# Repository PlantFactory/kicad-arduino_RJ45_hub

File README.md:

# kicad-arduino_RJ45_hub
The board implements 4 port I2C hub via RJ45.

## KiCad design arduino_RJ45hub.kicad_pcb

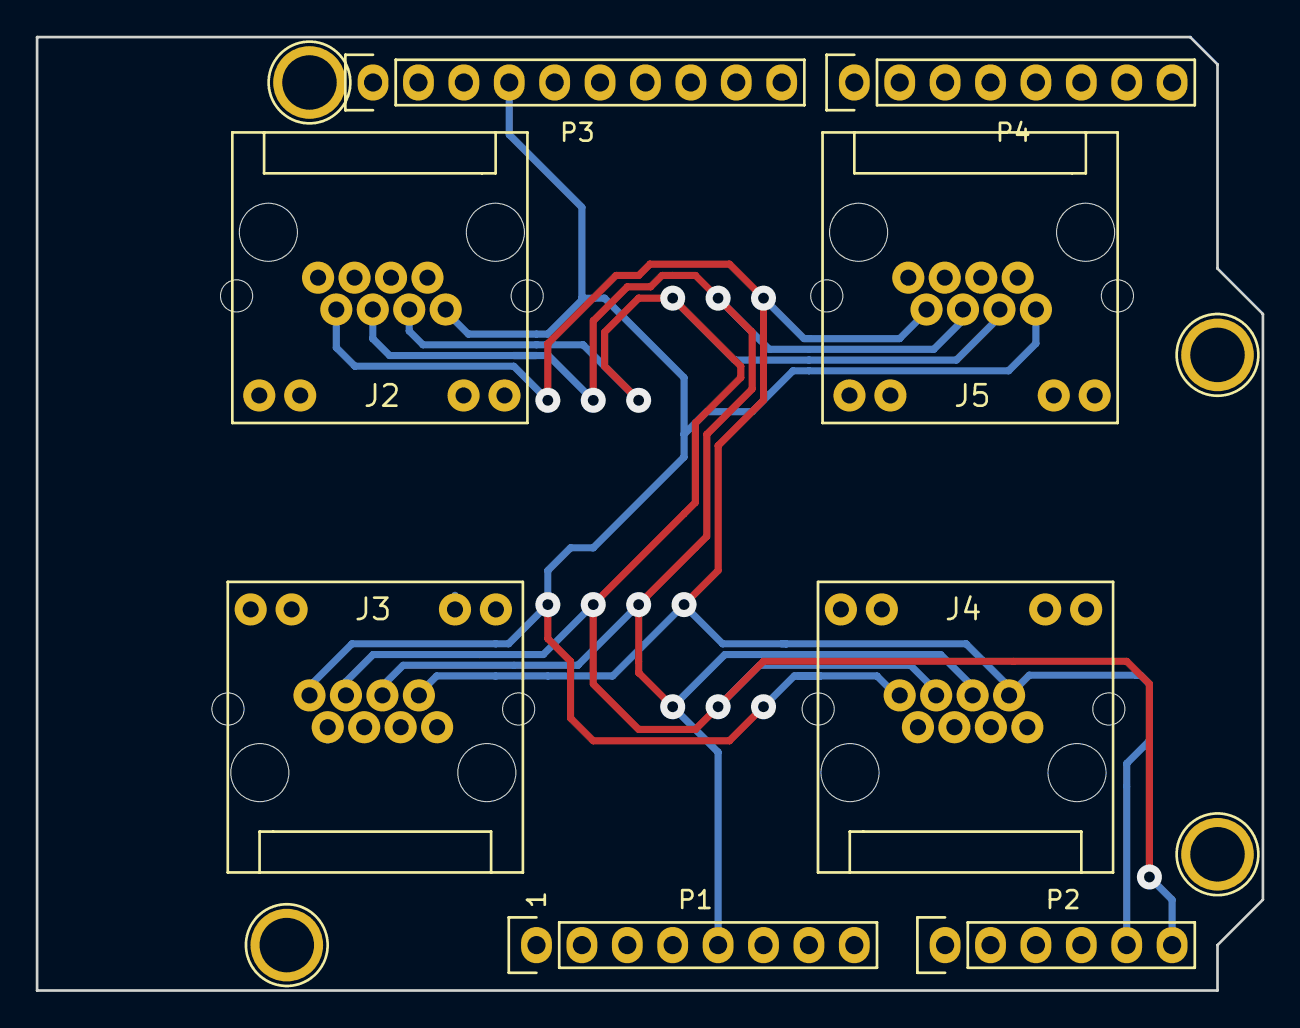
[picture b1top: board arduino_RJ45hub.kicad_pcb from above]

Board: 2 copper layers, 68.6 x 53.3 mm, 12 parts (0 on the bottom side), 16 nets.

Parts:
J2, J3, J4, J5: RJ45_LEDS; NewWays8p8c
P1: Power; Socket_Strip_Arduino_1x08
P2: Analog; Socket_Strip_Arduino_1x06
P3: Digital; Socket_Strip_Arduino_1x10
P4: Digital; Socket_Strip_Arduino_1x08
P5, P6, P7, P8: CONN_01X01; Arduino_1pin

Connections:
+5V: J2.5, J3.5, J4.5, J5.5, P1.5
/6(**): J5.9, P4.2
/7: J5.11, P4.1
/8: J4.9, P3.10
/9(**): J4.11, P3.9
/10(**/SS): J3.9, P3.8
/11(**/MOSI): J3.11, P3.7
/12(MISO): J2.9, P3.6
/13(SCK): J2.11, P3.5
/A4(SDA): J2.7, J3.7, J4.7, J5.7, P2.5
/A5(SCL): J2.3, J3.3, J4.3, J5.3, P2.6
GND: J2.1, J3.1, J4.1, J5.1, P3.4
unnamed: J2.2, J3.2, J4.2, J5.2
unnamed: J2.4, J3.4, J4.4, J5.4
unnamed: J2.6, J3.6, J4.6, J5.6
unnamed: J2.8, J3.8, J4.8, J5.8
